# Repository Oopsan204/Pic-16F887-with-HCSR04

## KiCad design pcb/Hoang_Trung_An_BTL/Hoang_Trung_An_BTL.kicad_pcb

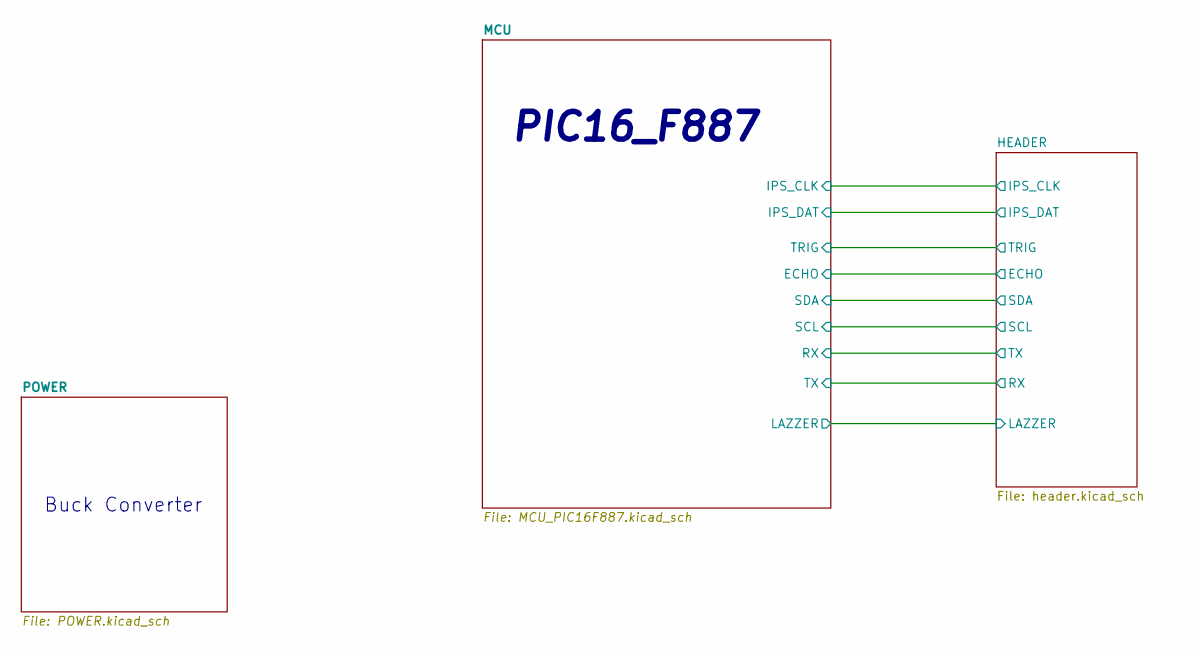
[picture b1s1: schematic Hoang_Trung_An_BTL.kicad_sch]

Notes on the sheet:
Buck Converter
PIC16_F887

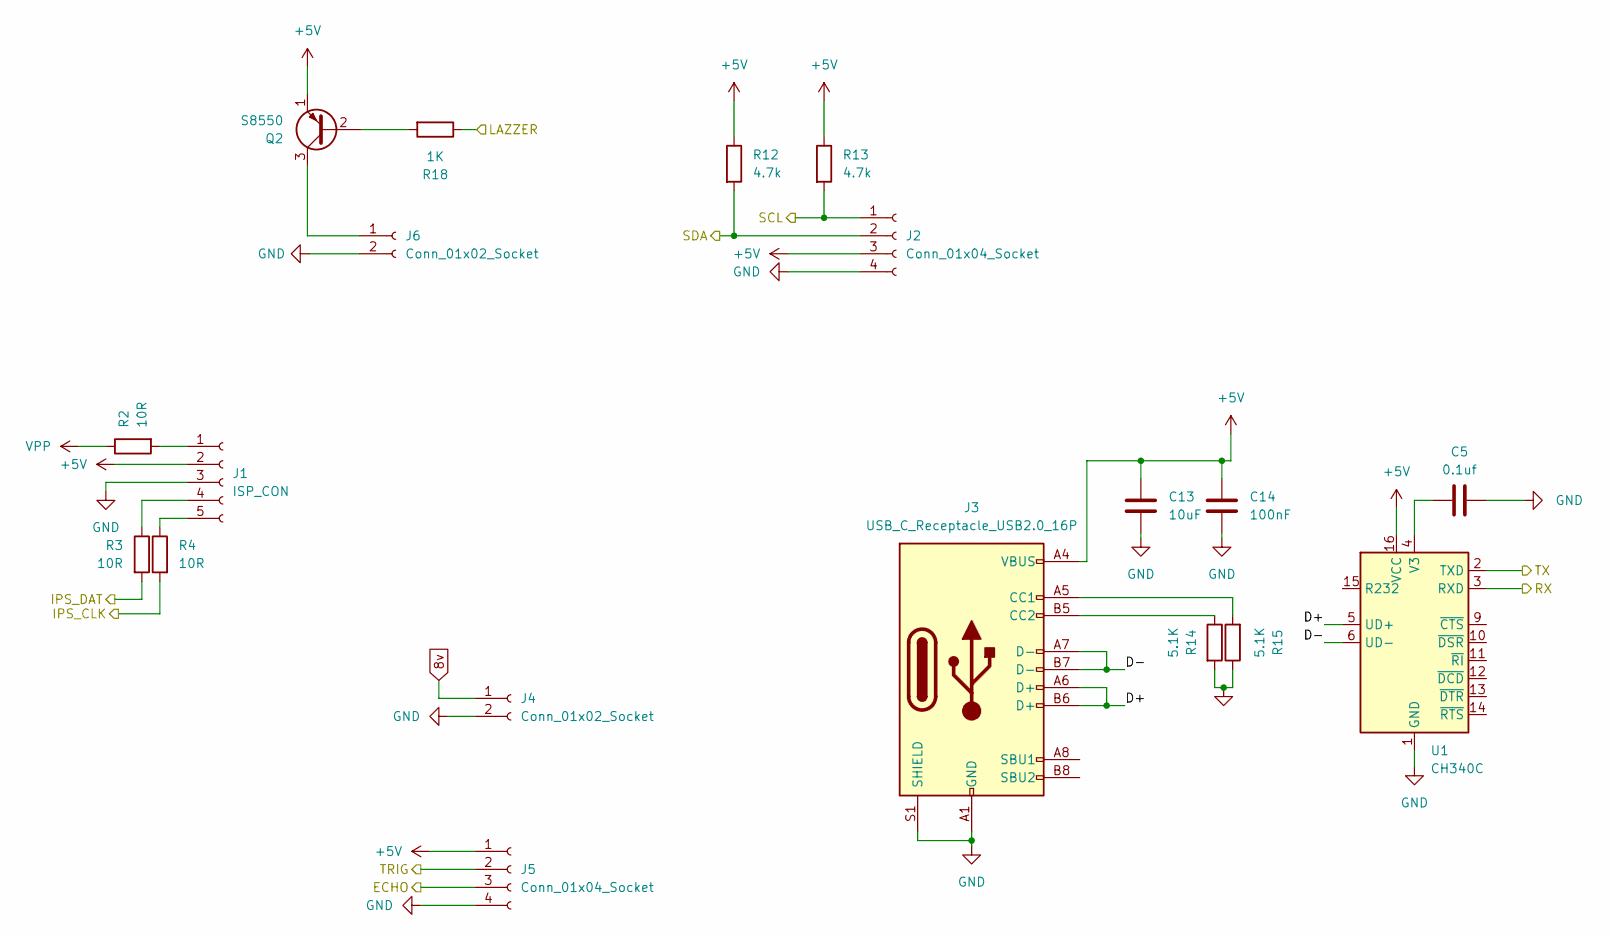
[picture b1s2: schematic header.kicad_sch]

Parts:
C5: 0.1uf
C13: 10uF; C_0603_1608Metric
C14: 100nF; C_0603_1608Metric
J1: ISP_CON; PinHeader_1x05_P2.54mm_Vertical
J2, J5: Conn_01x04_Socket; JST 4
J3: USB_C_Receptacle_USB2.0_16P; USB_C_Receptacle_GCT_USB4105-xx-A_16P_TopMnt_Horizontal
J4, J6: Conn_01x02_Socket; JST 2
Q2: S8550; SOT-23
R2, R3, R4: 10R; R_0603_1608Metric
R12, R13: 4.7k; R_0603_1608Metric
R14, R15: 5.1K; C_0603_1608Metric
R18: 1K; C_0603_1608Metric
U1: CH340C; SOIC-16_3.9x9.9mm_P1.27mm

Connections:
8v: J4.1; also elsewhere on the board
+5V: C13.1, C14.1, J1.2, J2.3, J3.A4 (VBUS), J3.A9 (VBUS), J3.B4 (VBUS), J3.B9 (VBUS), J5.1, Q2.1 (E), R12.1, R13.1, U1.16 (VCC); also elsewhere on the board
/HEADER/D+: J3.A6 (D+), J3.B6 (D+), U1.5 (UD+)
/HEADER/D-: J3.A7 (D-), J3.B7 (D-), U1.6 (UD-)
/HEADER/ECHO: J5.3; also elsewhere on the board
/HEADER/IPS_CLK: R4.2; also elsewhere on the board
/HEADER/IPS_DAT: R3.2; also elsewhere on the board
/HEADER/LAZZER: R18.1; also elsewhere on the board
/HEADER/RX: U1.3 (RXD); also elsewhere on the board
/HEADER/SCL: J2.1, R13.2; also elsewhere on the board
/HEADER/SDA: J2.2, R12.2; also elsewhere on the board
/HEADER/TRIG: J5.2; also elsewhere on the board
/HEADER/TX: U1.2 (TXD); also elsewhere on the board
GND: C5.2, C13.2, C14.2, J1.3, J2.4, J3.A1 (GND), J3.A12 (GND), J3.B1 (GND), J3.B12 (GND), J3.S1 (SHIELD), J4.2, J5.4, J6.2, R14.2, R15.1, U1.1 (GND); also elsewhere on the board
unnamed: C5.1, U1.4 (V3)
unnamed: J1.1, R2.2
unnamed: J1.4, R3.1
unnamed: J1.5, R4.1
unnamed: J3.A5 (CC1), R15.2
unnamed: J3.B5 (CC2), R14.1
unnamed: J6.1, Q2.3 (C)
unnamed: Q2.2 (B), R18.2
VPP: R2.1; also elsewhere on the board

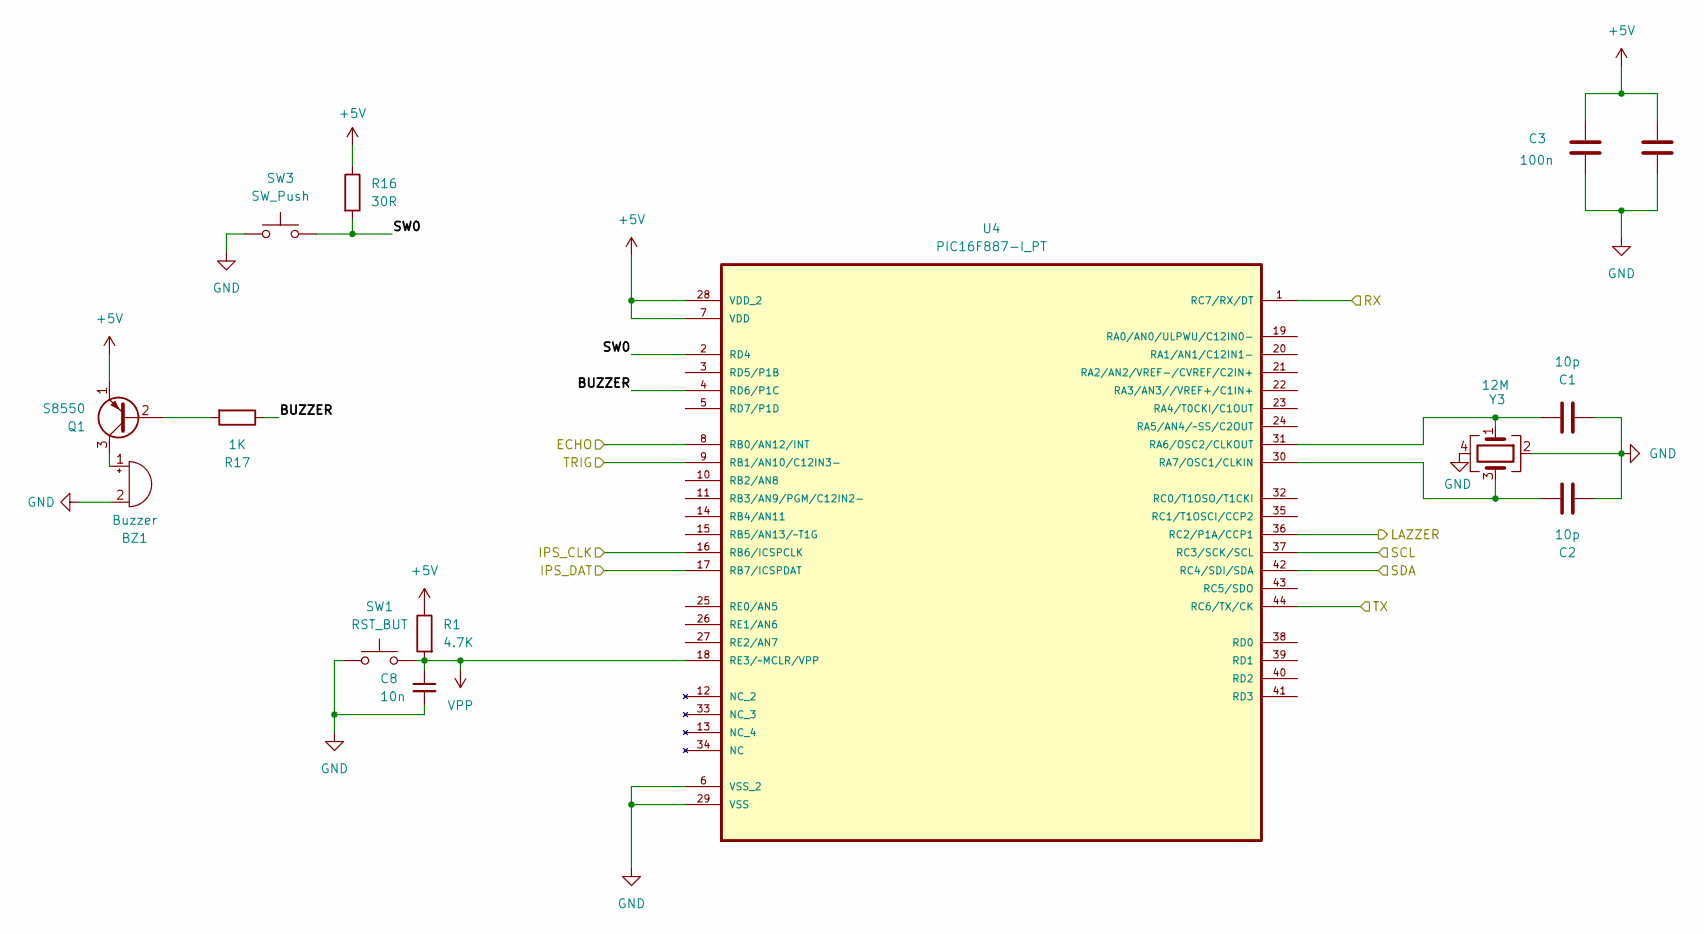
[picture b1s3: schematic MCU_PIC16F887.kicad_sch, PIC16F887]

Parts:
BZ1: Buzzer; buzzer tmb09a05 9x5.5
C1, C2: 10p; C_0603_1608Metric
C3, C4: 100n; C_0603_1608Metric
C8: 10n; C_0603_1608Metric
Q1: S8550; SOT-23
R1: 4.7K; R_0603_1608Metric
R16: 30R; C_0603_1608Metric
R17: 1K; C_0603_1608Metric
SW1: RST_BUT; SW_Tactile_SPST_NO_Straight_CK_PTS636Sx25SMTRLFS
SW3: SW_Push; SW_Tactile_SPST_NO_Straight_CK_PTS636Sx25SMTRLFS
U4: PIC16F887-I_PT; QFP80P1200X1200X120-44N; MPN PIC16F887-I/PT
Y3: 12M; Crystal_SMD_2520-4Pin_2.5x2.0mm

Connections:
+5V: C3.1, C4.1, Q1.1 (E), R1.1, R16.1, U4.7 (VDD), U4.28 (VDD_2); also elsewhere on the board
/HEADER/ECHO: U4.8 (RB0/AN12/INT); also elsewhere on the board
/HEADER/IPS_CLK: U4.16 (RB6/ICSPCLK); also elsewhere on the board
/HEADER/IPS_DAT: U4.17 (RB7/ICSPDAT); also elsewhere on the board
/HEADER/LAZZER: U4.36 (RC2/P1A/CCP1); also elsewhere on the board
/HEADER/RX: U4.44 (RC6/TX/CK); also elsewhere on the board
/HEADER/SCL: U4.37 (RC3/SCK/SCL); also elsewhere on the board
/HEADER/SDA: U4.42 (RC4/SDI/SDA); also elsewhere on the board
/HEADER/TRIG: U4.9 (RB1/AN10/C12IN3-); also elsewhere on the board
/HEADER/TX: U4.1 (RC7/RX/DT); also elsewhere on the board
/MCU/BUZZER: R17.1, U4.4 (RD6/P1C)
/MCU/SW0: R16.2, SW3.2, U4.2 (RD4)
GND: BZ1.2 (+), C1.1, C2.1, C3.2, C4.2, C8.2, SW1.1, SW3.1, U4.6 (VSS_2), U4.29 (VSS), Y3.2, Y3.4; also elsewhere on the board
unnamed: BZ1.1 (-), BZ1.3, Q1.3 (C)
unnamed: Q1.2 (B), R17.2
unnamed: C1.2, U4.31 (RA6/OSC2/CLKOUT), Y3.1
unnamed: C2.2, U4.30 (RA7/OSC1/CLKIN), Y3.3
VPP: C8.1, R1.2, SW1.2, U4.18 (RE3/~MCLR/VPP); also elsewhere on the board

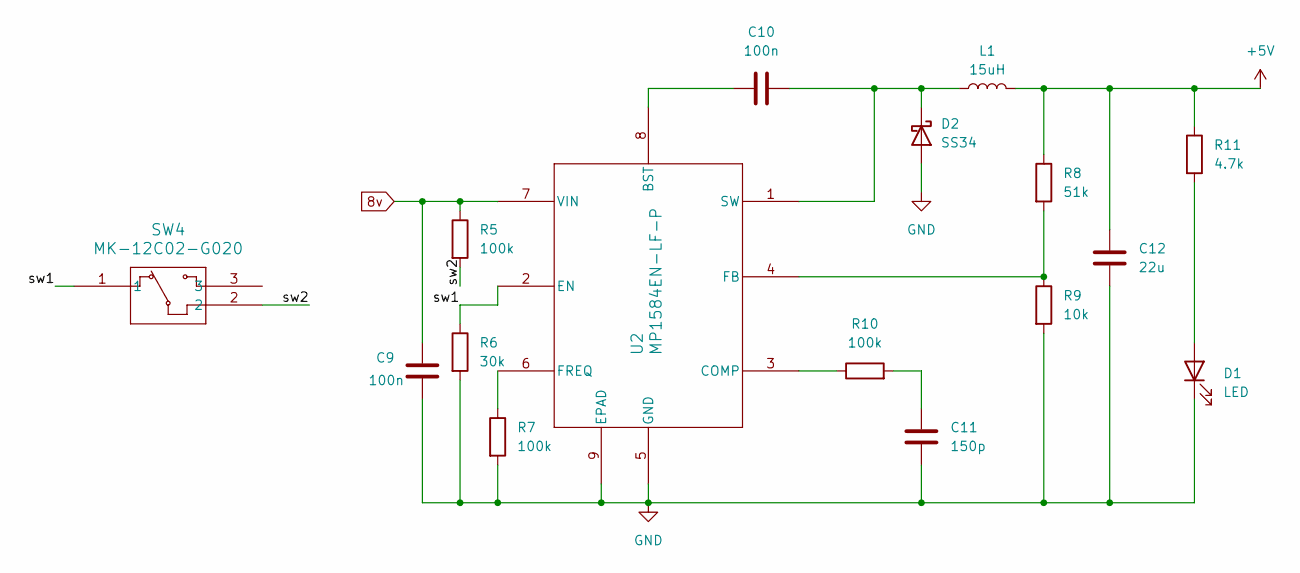
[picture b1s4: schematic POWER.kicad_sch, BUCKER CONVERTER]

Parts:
C9, C10: 100n; C_0603_1608Metric
C11: 150p; C_0603_1608Metric
C12: 22u; C_0603_1608Metric
D1: LED; LED_0603_1608Metric
D2: SS34; D_SMA
L1: 15uH; L_7.3x7.3_H3.5
R5, R7, R10: 100k; R_0603_1608Metric
R6: 30k; R_0603_1608Metric
R8: 51k; R_0603_1608Metric
R9: 10k; R_0603_1608Metric
R11: 4.7k; R_0603_1608Metric
SW4: MK-12C02-G020; MK-12C02-G020_GSW
U2: MP1584EN-LF-P; SOIC-8-1EP_3.9x4.9mm_P1.27mm_EP2.514x3.2mm_ThermalVias

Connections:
8v: C9.1, R5.1, U2.7 (VIN); also elsewhere on the board
+5V: C12.1, L1.2, R8.1, R11.1; also elsewhere on the board
/POWER/sw1: R6.1, SW4.1, U2.2 (EN)
/POWER/sw2: R5.2, SW4.2
GND: C9.2, C11.2, C12.2, D1.1 (K), D2.2 (A), R6.2, R7.2, R9.2, U2.5 (GND), U2.9 (EPAD); also elsewhere on the board
unnamed: C11.1, R10.2
unnamed: D1.2 (A), R11.2
unnamed: C10.1, D2.1 (K), L1.1, U2.1 (SW)
unnamed: C10.2, U2.8 (BST)
unnamed: R10.1, U2.3 (COMP)
unnamed: R8.2, R9.1, U2.4 (FB)
unnamed: R7.1, U2.6 (FREQ)

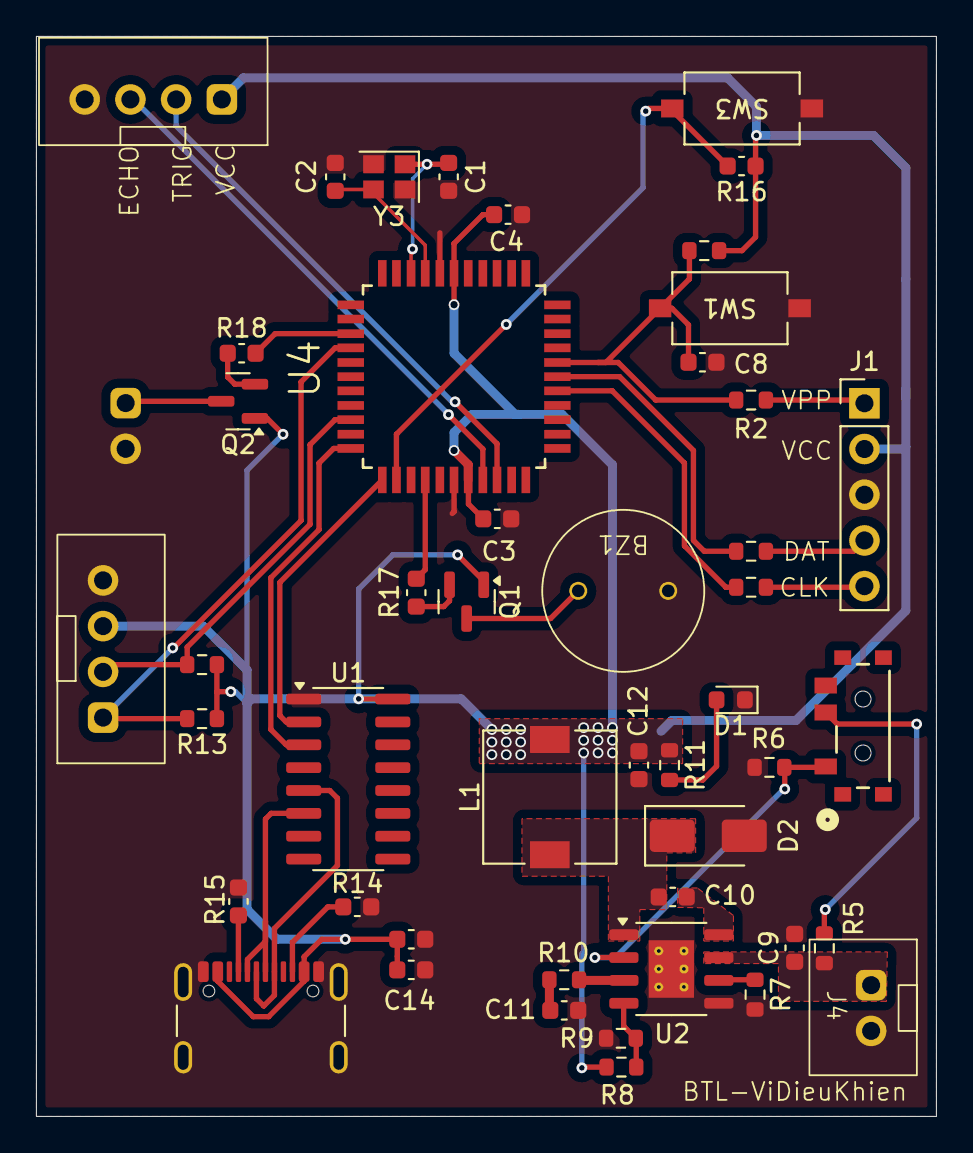
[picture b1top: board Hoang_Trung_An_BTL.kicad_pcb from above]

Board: 2 copper layers, 50.0 x 60.0 mm, 48 parts (1 on the bottom side), 37 nets.

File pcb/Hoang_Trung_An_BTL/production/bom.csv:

Designator,Footprint,Quantity,Value,LCSC Part #,,,mã sản phẩm
BZ1,buzzer tmb09a05 9x5.5,1,Buzzer,,,,CL08069
"C1, C2",603,2,10p,,,,CLA1296
"C10, C3, C4, C9",603,4,100n,,,,
C11,603,1,150p,,,,
C12,603,1,22u,,,,
C13,603,1,10uF,,,,
C14,603,1,100nF,,,,
C8,603,1,10n,,,,
D1,603,1,LED,,,,
D2,D_SMA,1,SS34,,,,
J1,PinHeader_1x05_P2.54mm_Vertical,1,ISP_CON,,,,
"J2, J5",JST 4,2,Conn_01x04_Socket,,,,
J3,USB_C_Receptacle_GCT_USB4105-xx-A_16P_TopMnt_Horizontal,1,USB_C_Receptacle_USB2.0_16P,,,,
"J4, J6",JST 2,2,Conn_01x02_Socket,,,,
L1,L_7.3x7.3_H3.5,1,15uH,,,,
"Q1, Q2",SOT-23,2,S8550,,,,
"R1, R11, R12, R13",603,4,4.7K,,,,
"R10, R5, R7",603,3,100k,,,,
"R14, R15",603,2,5.1K,,,,
"R16, R9",603,2,10K,,,,
"R17, R18",603,2,1K,,,,
"R2, R3, R4",603,3,10R,,,,
R6,603,1,30k,,,,
R8,603,1,51k,,,,
SW1,SW_Tactile_SPST_NO_Straight_CK_PTS636Sx25SMTRLFS,1,RST_BUT,,,,
SW3,SW_Tactile_SPST_NO_Straight_CK_PTS636Sx25SMTRLFS,1,SW_Push,,,,
SW4,MK-12C02-G020_GSW,1,MK-12C02-G020,,,,
U1,SOIC-16_3.9x9.9mm_P1.27mm,1,CH340C,,,,
U2,SOIC-8-1EP_3.9x4.9mm_P1.27mm_EP2.514x3.2mm_ThermalVias,1,MP1584EN-LF-P,,,,
U4,QFP80P1200X1200X120-44N,1,PIC16F887-I_PT,PIC16F887-I/PT,,,
Y3,Crystal_SMD_2520-4Pin_2.5x2.0mm,1,12M,,,,

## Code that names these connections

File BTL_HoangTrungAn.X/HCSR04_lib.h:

/* Microchip Technology Inc. and its subsidiaries.  You may use this software
 * and any derivatives exclusively with Microchip products.
 *
 * THIS SOFTWARE IS SUPPLIED BY MICROCHIP "AS IS".  NO WARRANTIES, WHETHER
 * EXPRESS, IMPLIED OR STATUTORY, APPLY TO THIS SOFTWARE, INCLUDING ANY IMPLIED
 * WARRANTIES OF NON-INFRINGEMENT, MERCHANTABILITY, AND FITNESS FOR A
 * PARTICULAR PURPOSE, OR ITS INTERACTION WITH MICROCHIP PRODUCTS, COMBINATION
 * WITH ANY OTHER PRODUCTS, OR USE IN ANY APPLICATION.
 *
 * IN NO EVENT WILL MICROCHIP BE LIABLE FOR ANY INDIRECT, SPECIAL, PUNITIVE,
 * INCIDENTAL OR CONSEQUENTIAL LOSS, DAMAGE, COST OR EXPENSE OF ANY KIND
 * WHATSOEVER RELATED TO THE SOFTWARE, HOWEVER CAUSED, EVEN IF MICROCHIP HAS
 * BEEN ADVISED OF THE POSSIBILITY OR THE DAMAGES ARE FORESEEABLE.  TO THE
 * FULLEST EXTENT ALLOWED BY LAW, MICROCHIP'S TOTAL LIABILITY ON ALL CLAIMS
 * IN ANY WAY RELATED TO THIS SOFTWARE WILL NOT EXCEED THE AMOUNT OF FEES, IF
 * ANY, THAT YOU HAVE PAID DIRECTLY TO MICROCHIP FOR THIS SOFTWARE.
 *
 * MICROCHIP PROVIDES THIS SOFTWARE CONDITIONALLY UPON YOUR ACCEPTANCE OF THESE
 * TERMS.
 */

/*
 * File:HCSR04_lib
 * Author: oopsan1112
 * Comments:
 * Revision history:
 */

// This is a guard condition so that contents of this file are not included
// more than once.
#ifndef HCSR04_LIB_H
#define HCSR04_LIB_H

#include <xc.h> // include processor files - each processor file is guarded.
#include "I2C_LCD.h"
#include "BUZZER.h"
#include "UART.h"
#include <stdbool.h>
#include <stdio.h>
#include <stdlib.h>

// TODO Insert appropriate #include <>

// TODO Insert C++ class definitions if appropriate

// TODO Insert declarations

// Comment a function and leverage automatic documentation with slash star star
/**
    <p><b>Function prototype:</b></p>

    <p><b>Summary:</b></p>

    <p><b>Description:</b></p>

    <p><b>Precondition:</b></p>

    <p><b>Parameters:</b></p>

    <p><b>Returns:</b></p>

    <p><b>Example:</b></p>
    <code>

    </code>

    <p><b>Remarks:</b></p>
 */
// TODO Insert declarations or function prototypes (right here) to leverage
// live documentation

#ifdef __cplusplus
extern "C"
{
#endif /* __cplusplus */

    // TODO If C++ is being used, regular C code needs function names to have C
    // linkage so the functions can be used by the c code.
#define _XTAL_FREQ 12000000

    int distn = 0;
    char out[20] = {0};

#define TRIG RB1
#define ECHO RB0
//------------------------------------------------------------------------------
#define TRIG_dir TRISB1
#define ECHO_dir TRISB0


//------------------------------------------------------------------------------
#define ECHO_ioc IOCB0

    void
    SR04_init(void);
    void SR04_trigger(void);
    void SR04_Distance(void);
#ifdef __cplusplus
}
#endif /* __cplusplus */

#endif /* XC_HEADER_TEMPLATE_H */

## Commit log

2025-03-25 final
2025-03-25 done
